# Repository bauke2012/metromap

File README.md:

# metromap
Live metro tracker board

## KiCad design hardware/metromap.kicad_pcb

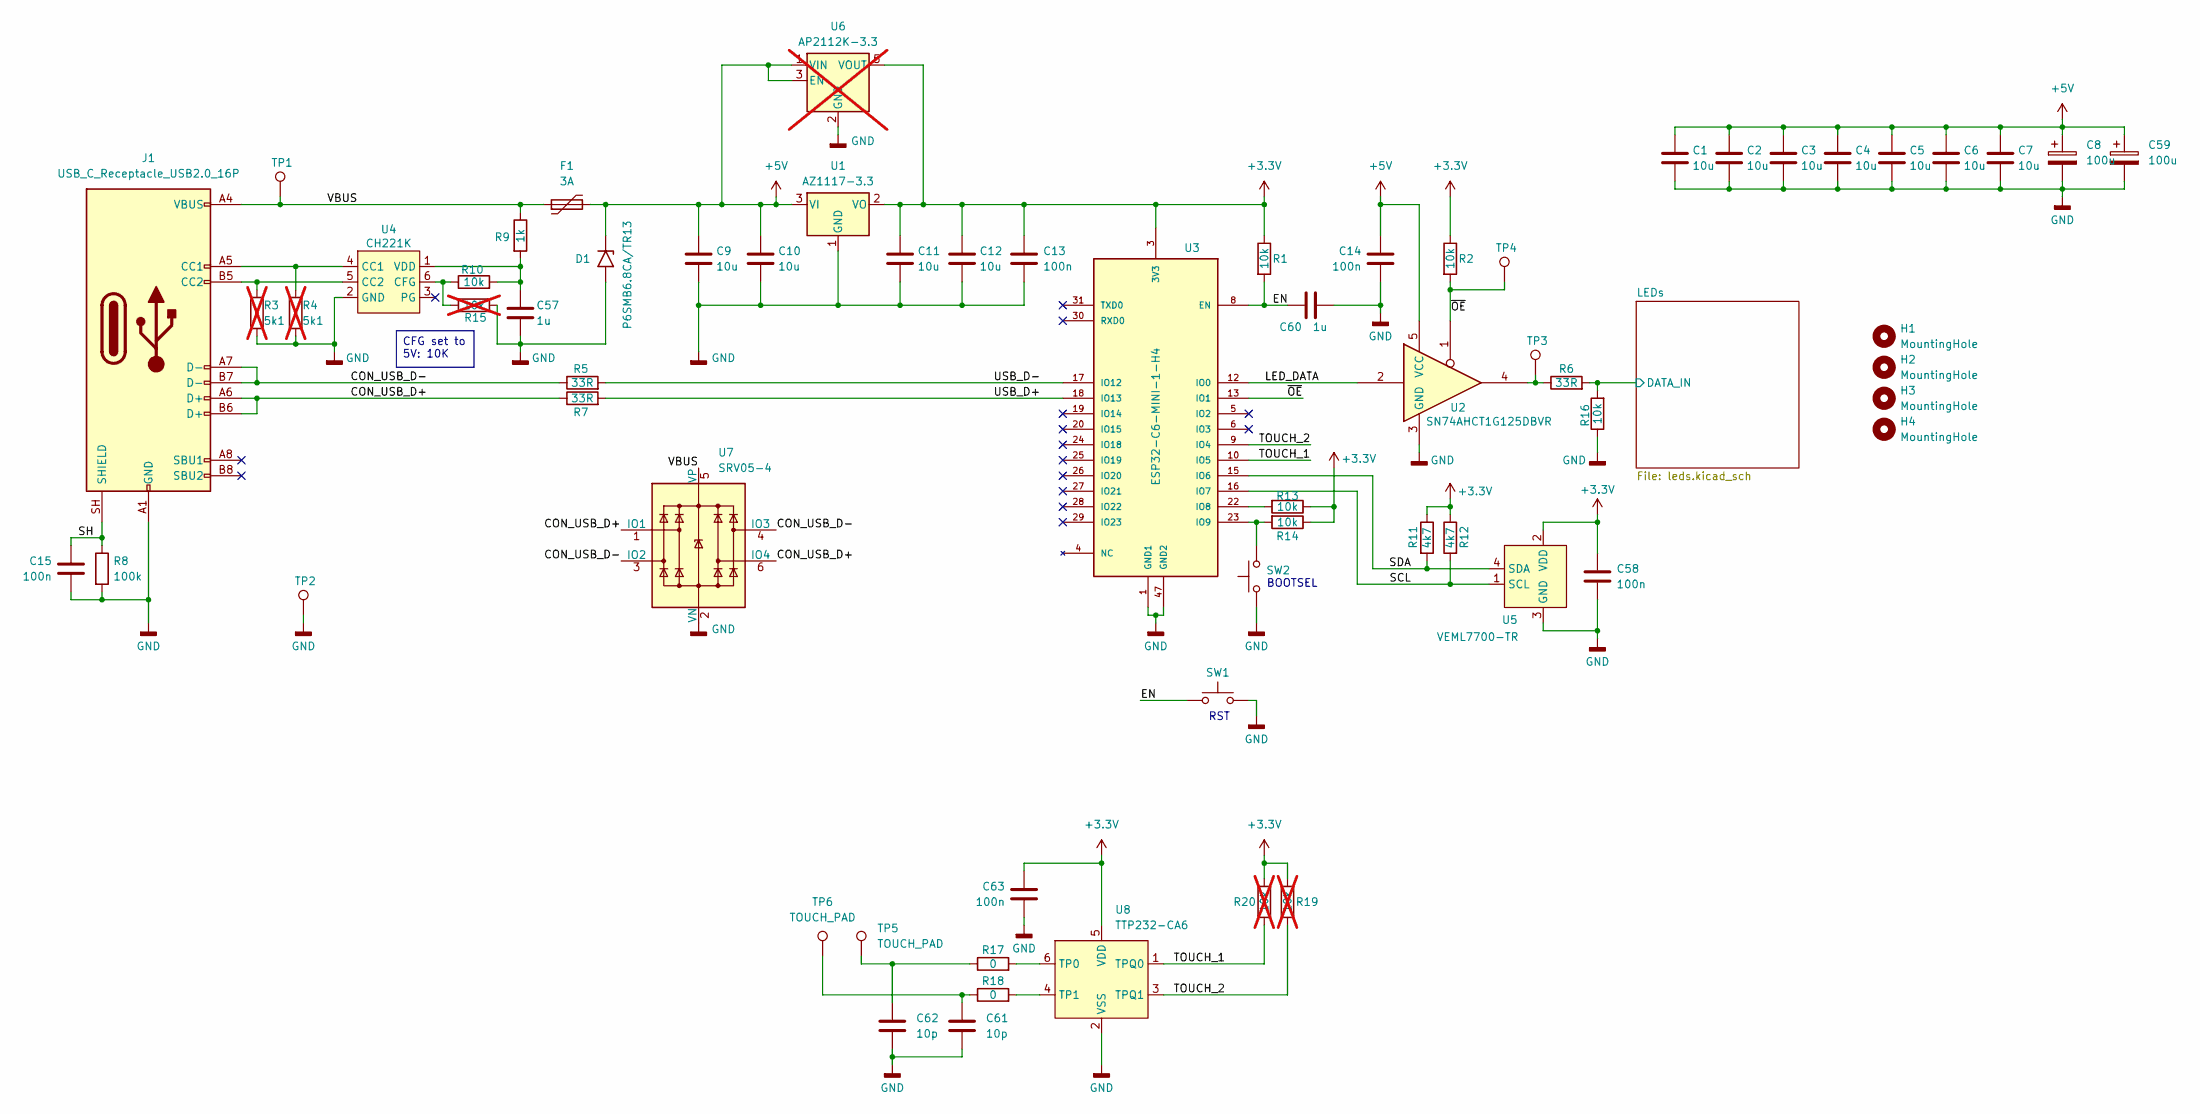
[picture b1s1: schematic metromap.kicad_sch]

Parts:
C1, C2, C3, C4, C5, C6, C7, C9, C10, C11, C12: 10u; C_0805_2012Metric; Manufacturer Part Name 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 CL21A106KAYNNNE; Digikey Part Number 1276-6456-1-ND
C8, C59: 100u; CP_Elec_6.3x7.7; Manufacturer Part Name 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 RVT1V101M0607; Digikey Part Number 732-6390-1-ND
C13, C14, C15, C58, C63: 100n; C_0402_1005Metric; Manufacturer Part Name 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 CL05B104KO5NNNC; Digikey Part Number 1276-1003-1-ND
C57, C60: 1u; C_0603_1608Metric; Manufacturer Part Name 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 CL10A105KB8NNNC; JLCPCB Part Number C15849
C61, C62: 10p; C_0603_1608Metric; Manufacturer Part Name 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 0603CG100J500NT; JLCPCB Part Number C1634
D1: P6SMB6.8CA/TR13; D_SMB; Manufacturer Part Name 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 P6SMB6.8CA/TR13; JLCPCB Part Number C78395
F1: 3A; Fuse_1812_4532Metric; Manufacturer Part Name 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 SMD1812B300TFT; JLCPCB Part Number C269149
H1, H2, H3, H4: MountingHole; MountingHole_3.2mm_M3
J1: USB_C_Receptacle_USB2.0_16P; GCT_USB4800-03-A_REVA; Manufacturer Part Name 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 USB4800-03-A; Digikey Part Number 2073-USB4800-03-ACT-ND
R1, R2, R10, R13, R14, R16: 10k; R_0603_1608Metric; Manufacturer Part Name 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 0603WAF1002T5E; JLCPCB Part Number C25804
R3, R4: 5k1; R_0603_1608Metric; Manufacturer Part Name 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 0603WAF5101T5E; Digikey Part Number 311-5.10KHRCT-ND; not fitted
R5, R7: 33R; R_0603_1608Metric; Manufacturer Part Name 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 0603WAF330JT5E; Digikey Part Number 13-RC0603FR-0733RLCT-ND
R6: 33R; R_0603_1608Metric; Manufacturer Part Name 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 0603WAF330JT5E; JLCPCB Part Number C23140
R8: 100k; R_0603_1608Metric; Manufacturer Part Name 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 0603WAF1003T5E; JLCPCB Part Number C25803
R9: 1k; R_0603_1608Metric; Manufacturer Part Name 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 0603WAF1001T5E; JLCPCB Part Number C21190
R11, R12: 4k7; R_0603_1608Metric; Manufacturer Part Name 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 0603WAF4701T5E; JLCPCB Part Number C23162
R15, R19, R20: 10k; R_0603_1608Metric; Manufacturer Part Name 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 0603WAF1002T5E; JLCPCB Part Number C25804; not fitted
R17, R18: 0; R_0603_1608Metric; Manufacturer Part Name 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 0603WAF0000T5E; JLCPCB Part Number C21189
SW1, SW2: XUNPU_TS-1088-AR02016; TS-1088-AR02016; Manufacturer Part Name 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 TS-1088-AR02016; JLCPCB Part Number C720477
TP1, TP2, TP3, TP4: TestPoint_Pad_D2.0mm
TP5, TP6: TOUCH_PAD
U1: AZ1117-3.3; SOT-223-3_TabPin2; Manufacturer Part Name 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 AMS1117-3.3; Digikey Part Number AZ1117CH-3.3TRG1DICT-ND
U2: SN74AHCT1G125DBVR; SOT-23-5; Manufacturer Part Name 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 SN74AHCT1G125DBVR; JLCPCB Part Number C7484
U3: ESP32-C6-MINI-1-H4; XCVR_ESP32-C6-MINI-1-H4; Manufacturer Part Name 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 ESP32-C6-MINI-1-H4; Digikey Part Number 1965-ESP32-C6-MINI-1-H4CT-ND
U4: CH221K; SOT-23-6; Manufacturer Part Name 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 CH221K; JLCPCB Part Number C5125736
U5: VEML7700-TR; XDCR_VEML7700-TR; Manufacturer Part Name 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 VEML7700-TR; JLCPCB Part Number C504893
U6: AP2112K-3.3; SOT-23-5; Manufacturer Part Name 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 AP2112K-3.3TRG1; JLCPCB Part Number C51118; not fitted
U7: SRV05-4; SOT-23-6; Manufacturer Part Name 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 SRV05-4-P-T7; JLCPCB Part Number C85364
U8: TTP232-CA6; SOT-23-6; Manufacturer Part Name 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 TTP232-CA6; JLCPCB Part Number C134176

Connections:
+3.3V: C11.1, C12.1, C13.1, C58.1, C63.1, R1.1, R2.1, R11.1, R12.1, R13.1, R14.1, R19.1, R20.1, U1.2 (VO), U3.3 (3V3), U5.2 (VDD), U6.5 (VOUT), U8.5 (VDD)
+5V: C1.1, C2.1, C3.1, C4.1, C5.1, C6.1, C7.1, C8.1, C9.1, C10.1, C14.1, C59.1, D1.1 (A1), F1.2, U1.3 (VI), U2.5 (VCC), U6.1 (VIN), U6.3 (EN); also elsewhere on the board
/CON_USB_D+: J1.A6 (D+), J1.B6 (D+), R7.1, U7.1 (IO1), U7.6 (IO4)
/CON_USB_D-: J1.A7 (D-), J1.B7 (D-), R5.1, U7.3 (IO2), U7.4 (IO3)
/EN: C60.1, R1.2, SW1.1, U3.8 (EN)
/LED_DATA: U2.2, U3.12 (IO0)
/LEDs/DATA_IN: R6.2, R16.2; also elsewhere on the board
/SCL: R12.2, U3.16 (IO7), U5.1 (SCL)
/SDA: R11.2, U3.15 (IO6), U5.4 (SDA)
/SH: C15.1, J1.SH (SHIELD), R8.1
/TOUCH_1: R20.2, U3.10 (IO5), U8.1 (TPQ0)
/TOUCH_2: R19.2, U3.9 (IO4), U8.3 (TPQ1)
/USB_D+: R7.2, U3.18 (IO13)
/USB_D-: R5.2, U3.17 (IO12)
/VBUS: F1.1, J1.A4 (VBUS), J1.A9 (VBUS), J1.B4 (VBUS), J1.B9 (VBUS), R9.1, TP1.1 (1_1), U7.5 (VP)
/~OE: R2.2, TP4.1 (1_1), U2.1, U3.13 (IO1)
GND: C1.2, C2.2, C3.2, C4.2, C5.2, C6.2, C7.2, C8.2, C9.2, C10.2, C11.2, C12.2, C13.2, C14.2, C15.2, C57.2, C58.2, C59.2, C60.2, C61.2, C62.2, C63.2, D1.2 (A2), J1.A1 (GND), J1.A12 (GND), J1.B1 (GND), J1.B12 (GND), R3.2, R4.2, R8.2, R15.1, R16.1, SW1.2, SW2.1, TP2.1 (1_1), U1.1 (GND), U2.3 (GND), U3.1 (GND1), U3.2 (GND1), U3.11 (GND1), U3.14 (GND1), U3.36 (GND1), U3.37 (GND1), U3.38 (GND1), U3.39 (GND1), U3.40 (GND1), U3.41 (GND1), U3.42 (GND1), U3.43 (GND1), U3.44 (GND1), U3.45 (GND1), U3.46 (GND1), U3.47 (GND2), U3.48 (GND2), U3.49_1 (GND2), U3.49_2 (GND2), U3.49_3 (GND2), U3.49_4 (GND2), U3.49_5 (GND2), U3.49_6 (GND2), U3.49_7 (GND2), U3.49_8 (GND2), U3.49_9 (GND2), U3.50 (GND2), U3.51 (GND2), U3.52 (GND2), U3.53 (GND2), U4.2 (GND), U5.3 (GND), U6.2 (GND), U7.2 (VN), U8.2 (VSS); also elsewhere on the board
unnamed: C61.1, R18.1, TP6.1 (1_1)
unnamed: C62.1, R17.1, TP5.1 (1_1)
unnamed: J1.A5 (CC1), R4.1, U4.4 (CC1)
unnamed: J1.B5 (CC2), R3.1, U4.5 (CC2)
unnamed: R6.1, TP3.1 (1_1), U2.4
unnamed: R13.2, U3.22 (IO8)
unnamed: R14.2, SW2.2, U3.23 (IO9)
unnamed: R10.1, R15.2, U4.6 (CFG)
unnamed: C57.1, R9.2, R10.2, U4.1 (VDD)
unnamed: R17.2, U8.6 (TP0)
unnamed: R18.2, U8.4 (TP1)

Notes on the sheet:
RST
BOOTSEL
CFG set to 5V: 10K

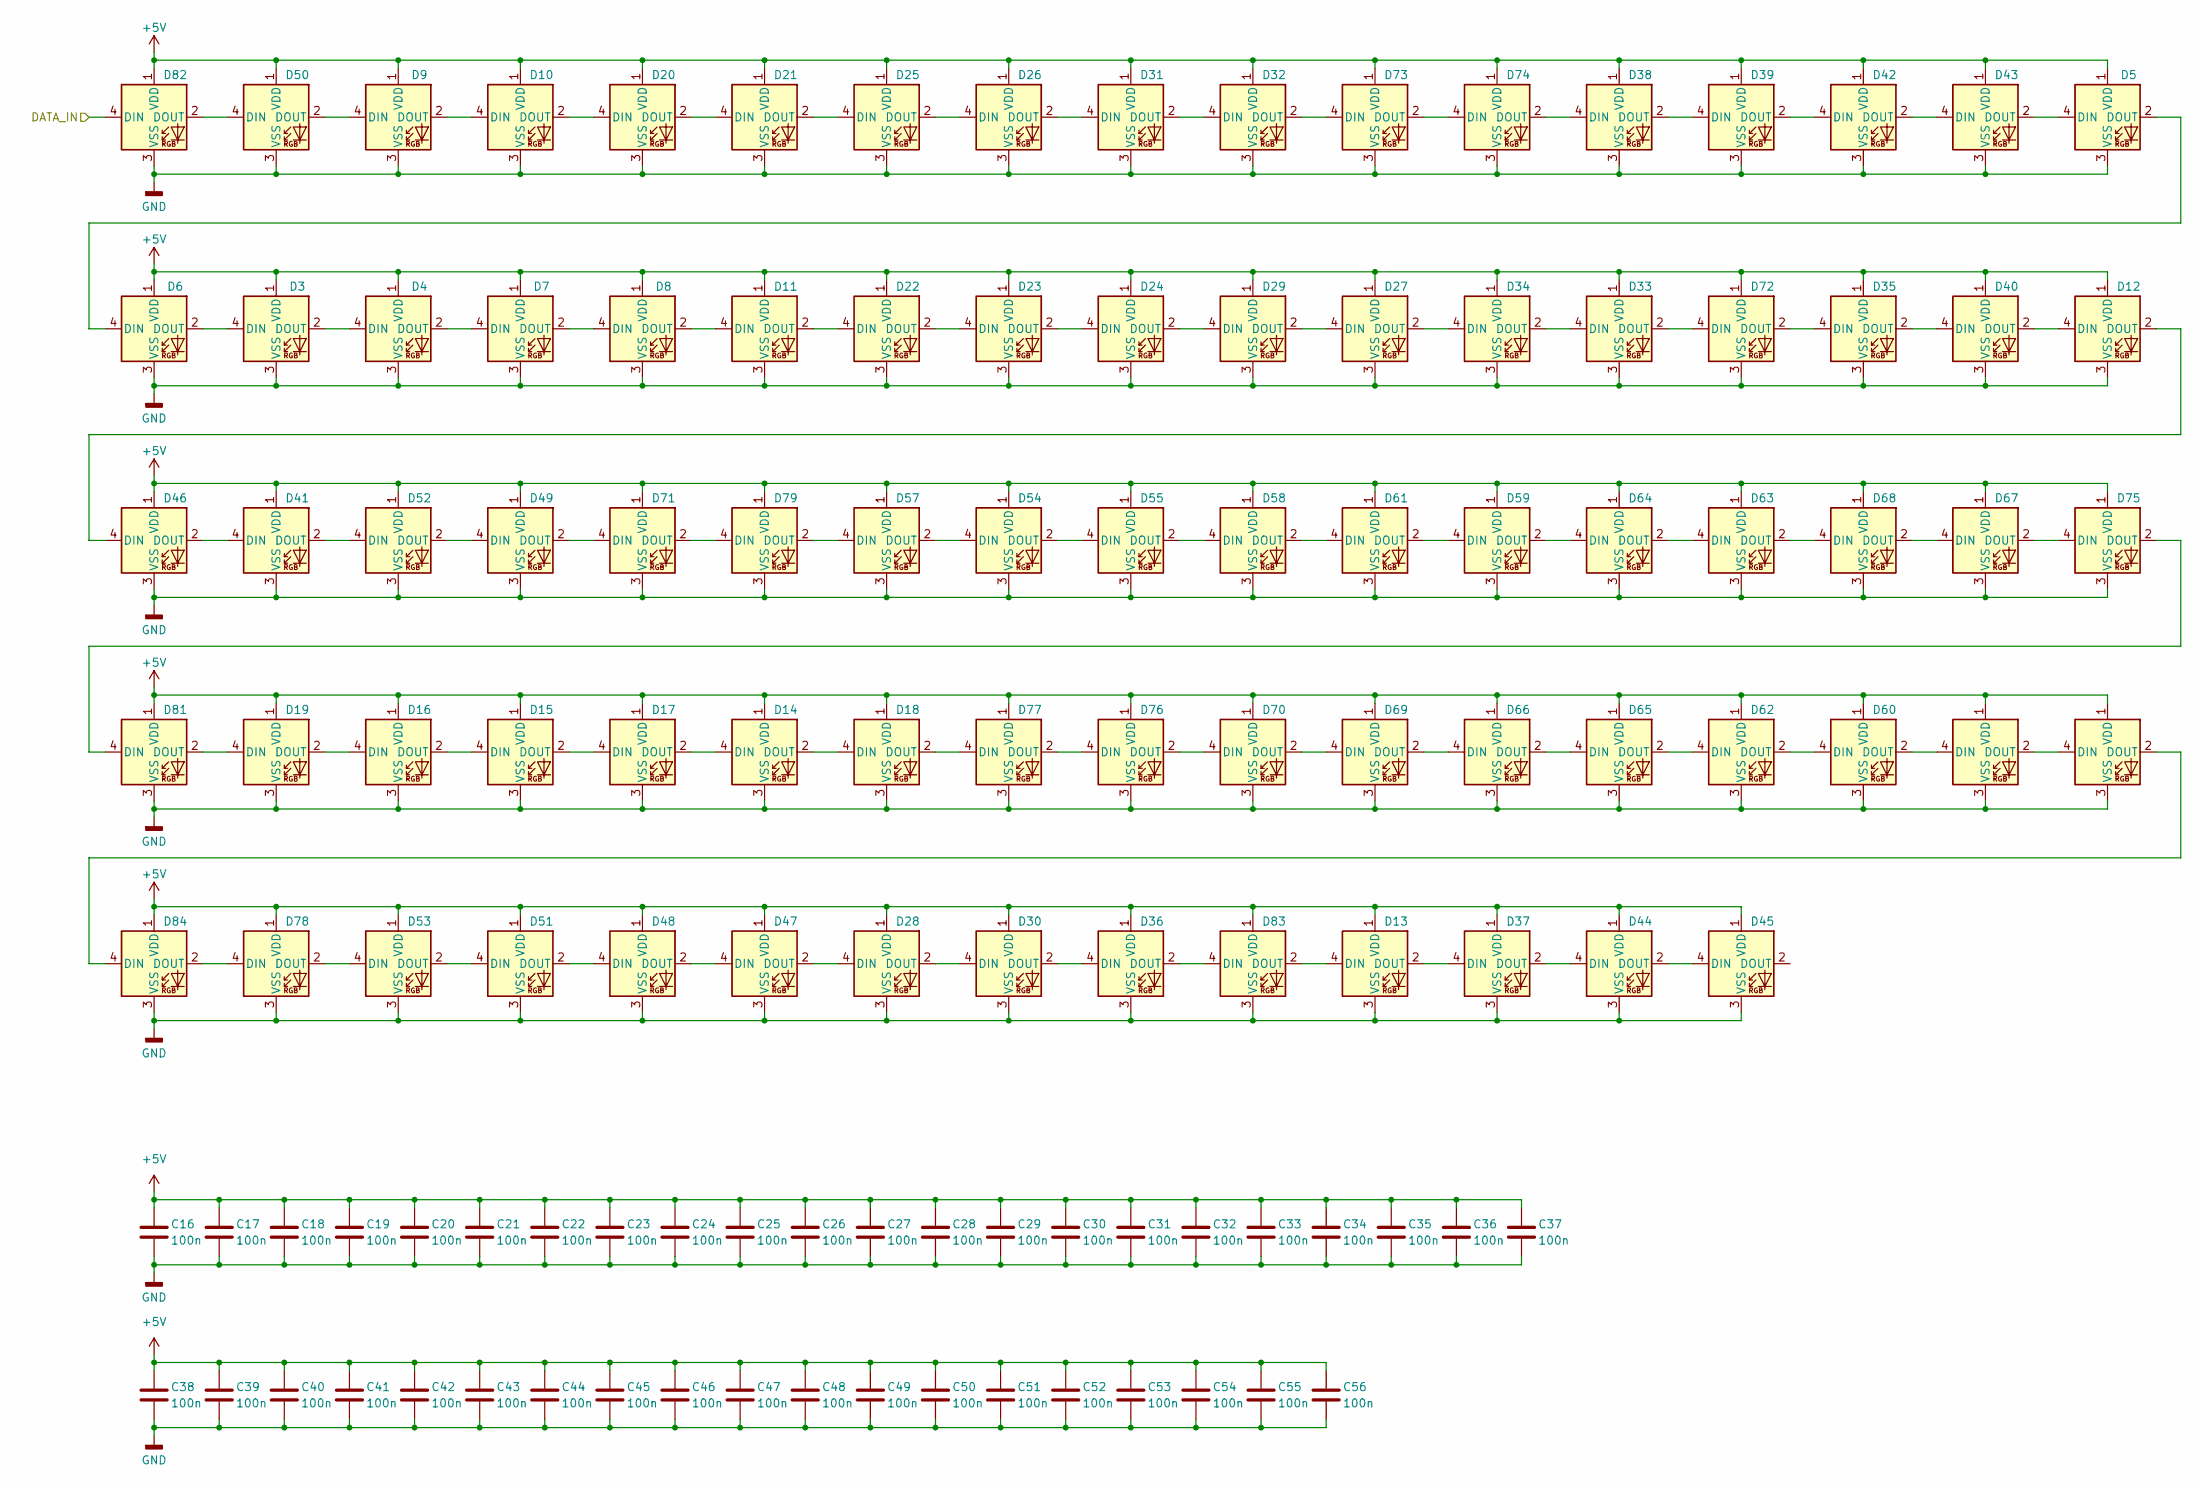
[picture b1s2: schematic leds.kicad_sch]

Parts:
C16, C17, C18, C19, C20, C21, C22, C23, C24, C25, C26, C27, C28, C29, C30, C31, C32, C33, C34, C35, C36, C37, C38, C39, C40, C41, C42, C43, C44, C45, C46, C47, C48, C49, C50, C51, C52, C53, C54, C55, C56: 100n; C_0402_1005Metric; Manufacturer Part Name 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 CL05B104KO5NNNC; Digikey Part Number 1276-1003-1-ND
D3, D4, D5, D6, D7, D8, D9, D10, D11, D12, D13, D14, D15, D16, D17, D18, D19, D20, D21, D22, D23, D24, D25, D26, D27, D28, D29, D30, D31, D32, D33, D34, D35, D36, D37, D38, D39, D40, D41, D42, D43, D44, D45, D46, D47, D48, D49, D50, D51, D52, D53, D54, D55, D56, D57, D58, D59, D60, D61, D62, D63, D64, D65, D66, D67, D68, D69, D70, D71, D72, D73, D74, D75, D76, D77, D78, D79, D80, D81, D82, D83, D84: SK6812-EC20; RGB_LED_2020; Manufacturer Part Name 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 SK6812-EC20; Digikey Part Number 1830-IN-PI20TAT5R5G5BCT-ND

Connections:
+5V: C16.1, C17.1, C18.1, C19.1, C20.1, C21.1, C22.1, C23.1, C24.1, C25.1, C26.1, C27.1, C28.1, C29.1, C30.1, C31.1, C32.1, C33.1, C34.1, C35.1, C36.1, C37.1, C38.1, C39.1, C40.1, C41.1, C42.1, C43.1, C44.1, C45.1, C46.1, C47.1, C48.1, C49.1, C50.1, C51.1, C52.1, C53.1, C54.1, C55.1, C56.1, D3.1 (VDD), D4.1 (VDD), D5.1 (VDD), D6.1 (VDD), D7.1 (VDD), D8.1 (VDD), D9.1 (VDD), D10.1 (VDD), D11.1 (VDD), D12.1 (VDD), D13.1 (VDD), D14.1 (VDD), D15.1 (VDD), D16.1 (VDD), D17.1 (VDD), D18.1 (VDD), D19.1 (VDD), D20.1 (VDD), D21.1 (VDD), D22.1 (VDD), D23.1 (VDD), D24.1 (VDD), D25.1 (VDD), D26.1 (VDD), D27.1 (VDD), D28.1 (VDD), D29.1 (VDD), D30.1 (VDD), D31.1 (VDD), D32.1 (VDD), D33.1 (VDD), D34.1 (VDD), D35.1 (VDD), D36.1 (VDD), D37.1 (VDD), D38.1 (VDD), D39.1 (VDD), D40.1 (VDD), D41.1 (VDD), D42.1 (VDD), D43.1 (VDD), D44.1 (VDD), D45.1 (VDD), D46.1 (VDD), D47.1 (VDD), D48.1 (VDD), D49.1 (VDD), D50.1 (VDD), D51.1 (VDD), D52.1 (VDD), D53.1 (VDD), D54.1 (VDD), D55.1 (VDD), D56.1 (VDD), D57.1 (VDD), D58.1 (VDD), D59.1 (VDD), D60.1 (VDD), D61.1 (VDD), D62.1 (VDD), D63.1 (VDD), D64.1 (VDD), D65.1 (VDD), D66.1 (VDD), D67.1 (VDD), D68.1 (VDD), D69.1 (VDD), D70.1 (VDD), D71.1 (VDD), D72.1 (VDD), D73.1 (VDD), D74.1 (VDD), D75.1 (VDD), D76.1 (VDD), D77.1 (VDD), D78.1 (VDD), D79.1 (VDD), D80.1 (VDD), D81.1 (VDD), D82.1 (VDD), D83.1 (VDD), D84.1 (VDD); also elsewhere on the board
/LEDs/DATA_IN: D82.4 (DIN); also elsewhere on the board
GND: C16.2, C17.2, C18.2, C19.2, C20.2, C21.2, C22.2, C23.2, C24.2, C25.2, C26.2, C27.2, C28.2, C29.2, C30.2, C31.2, C32.2, C33.2, C34.2, C35.2, C36.2, C37.2, C38.2, C39.2, C40.2, C41.2, C42.2, C43.2, C44.2, C45.2, C46.2, C47.2, C48.2, C49.2, C50.2, C51.2, C52.2, C53.2, C54.2, C55.2, C56.2, D3.3 (VSS), D4.3 (VSS), D5.3 (VSS), D6.3 (VSS), D7.3 (VSS), D8.3 (VSS), D9.3 (VSS), D10.3 (VSS), D11.3 (VSS), D12.3 (VSS), D13.3 (VSS), D14.3 (VSS), D15.3 (VSS), D16.3 (VSS), D17.3 (VSS), D18.3 (VSS), D19.3 (VSS), D20.3 (VSS), D21.3 (VSS), D22.3 (VSS), D23.3 (VSS), D24.3 (VSS), D25.3 (VSS), D26.3 (VSS), D27.3 (VSS), D28.3 (VSS), D29.3 (VSS), D30.3 (VSS), D31.3 (VSS), D32.3 (VSS), D33.3 (VSS), D34.3 (VSS), D35.3 (VSS), D36.3 (VSS), D37.3 (VSS), D38.3 (VSS), D39.3 (VSS), D40.3 (VSS), D41.3 (VSS), D42.3 (VSS), D43.3 (VSS), D44.3 (VSS), D45.3 (VSS), D46.3 (VSS), D47.3 (VSS), D48.3 (VSS), D49.3 (VSS), D50.3 (VSS), D51.3 (VSS), D52.3 (VSS), D53.3 (VSS), D54.3 (VSS), D55.3 (VSS), D56.3 (VSS), D57.3 (VSS), D58.3 (VSS), D59.3 (VSS), D60.3 (VSS), D61.3 (VSS), D62.3 (VSS), D63.3 (VSS), D64.3 (VSS), D65.3 (VSS), D66.3 (VSS), D67.3 (VSS), D68.3 (VSS), D69.3 (VSS), D70.3 (VSS), D71.3 (VSS), D72.3 (VSS), D73.3 (VSS), D74.3 (VSS), D75.3 (VSS), D76.3 (VSS), D77.3 (VSS), D78.3 (VSS), D79.3 (VSS), D80.3 (VSS), D81.3 (VSS), D82.3 (VSS), D83.3 (VSS), D84.3 (VSS); also elsewhere on the board
unnamed: D3.4 (DIN), D6.2 (DOUT)
unnamed: D3.2 (DOUT), D4.4 (DIN)
unnamed: D4.2 (DOUT), D7.4 (DIN)
unnamed: D5.2 (DOUT), D6.4 (DIN)
unnamed: D7.2 (DOUT), D8.4 (DIN)
unnamed: D9.2 (DOUT), D10.4 (DIN)
unnamed: D10.2 (DOUT), D20.4 (DIN)
unnamed: D8.2 (DOUT), D11.4 (DIN)
unnamed: D11.2 (DOUT), D22.4 (DIN)
unnamed: D12.4 (DIN), D40.2 (DOUT)
unnamed: D12.2 (DOUT), D46.4 (DIN)
unnamed: D13.4 (DIN), D83.2 (DOUT)
unnamed: D13.2 (DOUT), D37.4 (DIN)
unnamed: D14.4 (DIN), D17.2 (DOUT)
unnamed: D14.2 (DOUT), D18.4 (DIN)
unnamed: D15.4 (DIN), D16.2 (DOUT)
unnamed: D15.2 (DOUT), D17.4 (DIN)
unnamed: D16.4 (DIN), D19.2 (DOUT)
unnamed: D18.2 (DOUT), D77.4 (DIN)
unnamed: D19.4 (DIN), D81.2 (DOUT)
unnamed: D20.2 (DOUT), D21.4 (DIN)
unnamed: D21.2 (DOUT), D25.4 (DIN)
unnamed: D22.2 (DOUT), D23.4 (DIN)
unnamed: D23.2 (DOUT), D24.4 (DIN)
unnamed: D24.2 (DOUT), D29.4 (DIN)
unnamed: D25.2 (DOUT), D26.4 (DIN)
unnamed: D26.2 (DOUT), D31.4 (DIN)
unnamed: D27.4 (DIN), D29.2 (DOUT)
unnamed: D27.2 (DOUT), D34.4 (DIN)
unnamed: D28.4 (DIN), D47.2 (DOUT)
unnamed: D28.2 (DOUT), D30.4 (DIN)
unnamed: D30.2 (DOUT), D36.4 (DIN)
unnamed: D31.2 (DOUT), D32.4 (DIN)
unnamed: D32.2 (DOUT), D73.4 (DIN)
unnamed: D33.4 (DIN), D34.2 (DOUT)
unnamed: D33.2 (DOUT), D72.4 (DIN)
unnamed: D35.4 (DIN), D72.2 (DOUT)
unnamed: D35.2 (DOUT), D40.4 (DIN)
unnamed: D36.2 (DOUT), D83.4 (DIN)
unnamed: D37.2 (DOUT), D44.4 (DIN)
unnamed: D38.4 (DIN), D74.2 (DOUT)
unnamed: D38.2 (DOUT), D39.4 (DIN)
unnamed: D39.2 (DOUT), D42.4 (DIN)
unnamed: D41.4 (DIN), D46.2 (DOUT)
unnamed: D41.2 (DOUT), D52.4 (DIN)
unnamed: D42.2 (DOUT), D43.4 (DIN)
unnamed: D5.4 (DIN), D43.2 (DOUT)
unnamed: D44.2 (DOUT), D45.4 (DIN)
unnamed: D47.4 (DIN), D48.2 (DOUT)
unnamed: D48.4 (DIN), D51.2 (DOUT)
unnamed: D49.4 (DIN), D52.2 (DOUT)
unnamed: D49.2 (DOUT), D71.4 (DIN)
unnamed: D50.4 (DIN), D82.2 (DOUT)
unnamed: D9.4 (DIN), D50.2 (DOUT)
unnamed: D51.4 (DIN), D53.2 (DOUT)
unnamed: D53.4 (DIN), D78.2 (DOUT)
unnamed: D54.4 (DIN), D57.2 (DOUT)
unnamed: D54.2 (DOUT), D55.4 (DIN)
unnamed: D55.2 (DOUT), D58.4 (DIN)
unnamed: D56.4 (DIN), D80.2 (DOUT)
unnamed: D56.2 (DOUT), D84.4 (DIN)
unnamed: D57.4 (DIN), D79.2 (DOUT)
unnamed: D58.2 (DOUT), D61.4 (DIN)
unnamed: D59.4 (DIN), D61.2 (DOUT)
unnamed: D59.2 (DOUT), D64.4 (DIN)
unnamed: D60.4 (DIN), D62.2 (DOUT)
unnamed: D60.2 (DOUT), D80.4 (DIN)
unnamed: D62.4 (DIN), D65.2 (DOUT)
unnamed: D63.4 (DIN), D64.2 (DOUT)
unnamed: D63.2 (DOUT), D68.4 (DIN)
unnamed: D65.4 (DIN), D66.2 (DOUT)
unnamed: D66.4 (DIN), D69.2 (DOUT)
unnamed: D67.4 (DIN), D68.2 (DOUT)
unnamed: D67.2 (DOUT), D75.4 (DIN)
unnamed: D69.4 (DIN), D70.2 (DOUT)
unnamed: D70.4 (DIN), D76.2 (DOUT)
unnamed: D71.2 (DOUT), D79.4 (DIN)
unnamed: D73.2 (DOUT), D74.4 (DIN)
unnamed: D75.2 (DOUT), D81.4 (DIN)
unnamed: D76.4 (DIN), D77.2 (DOUT)
unnamed: D78.4 (DIN), D84.2 (DOUT)

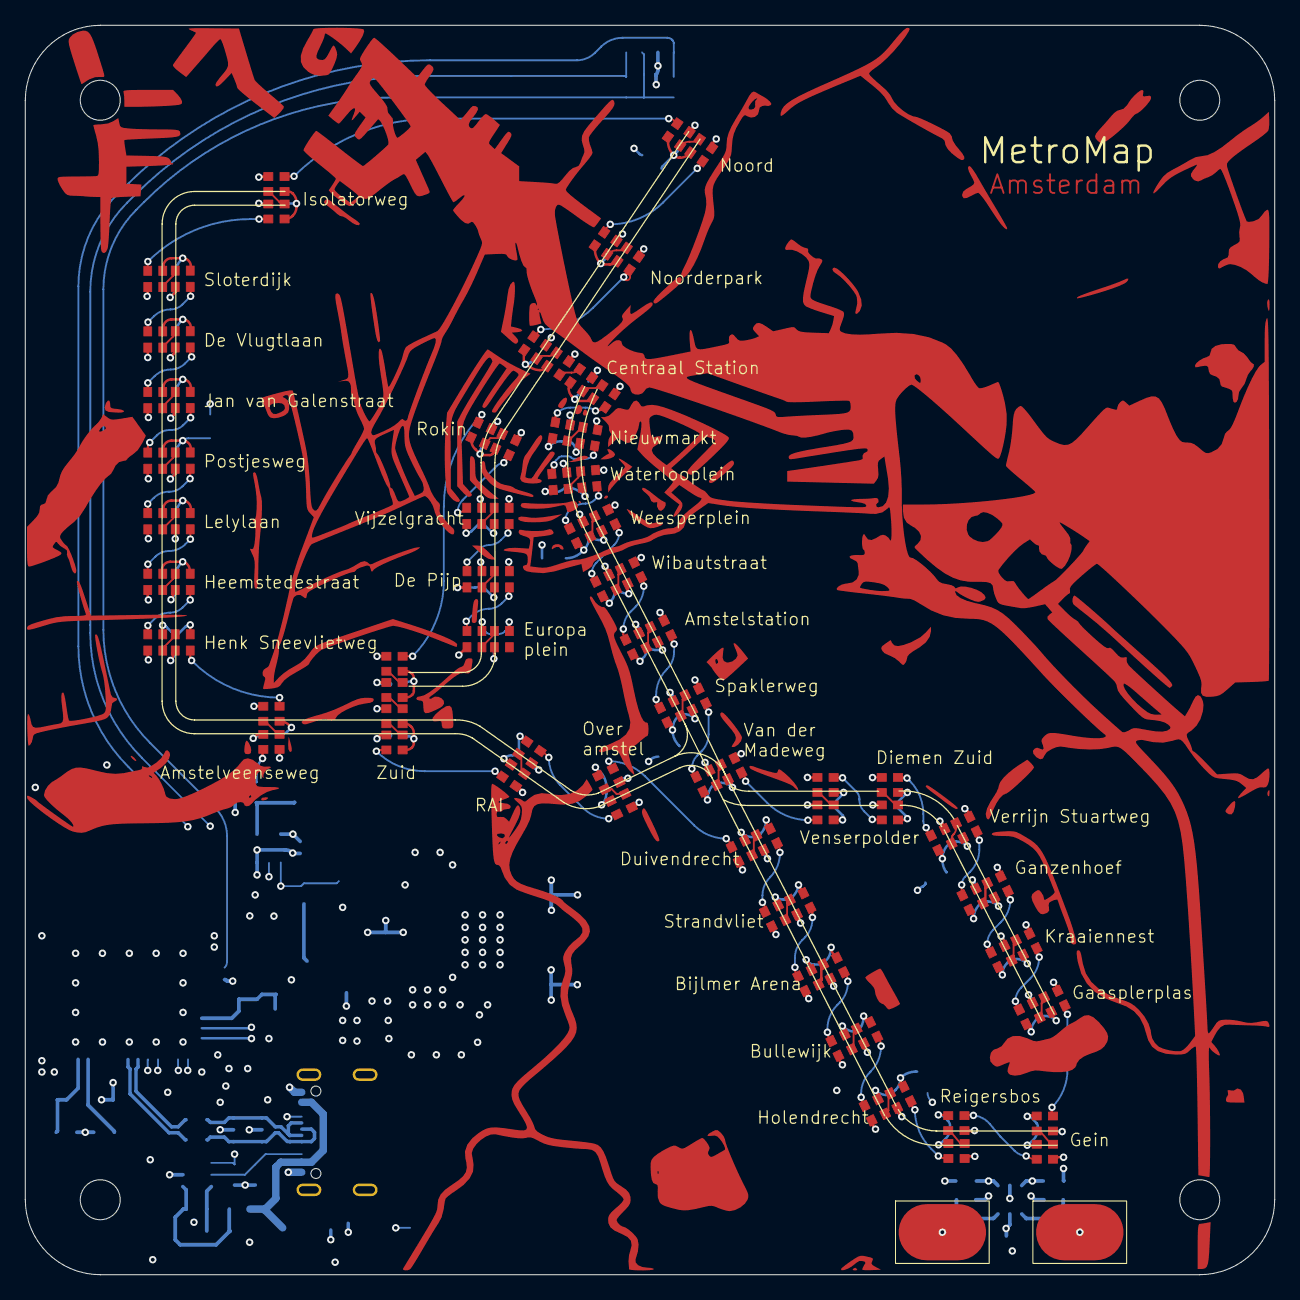
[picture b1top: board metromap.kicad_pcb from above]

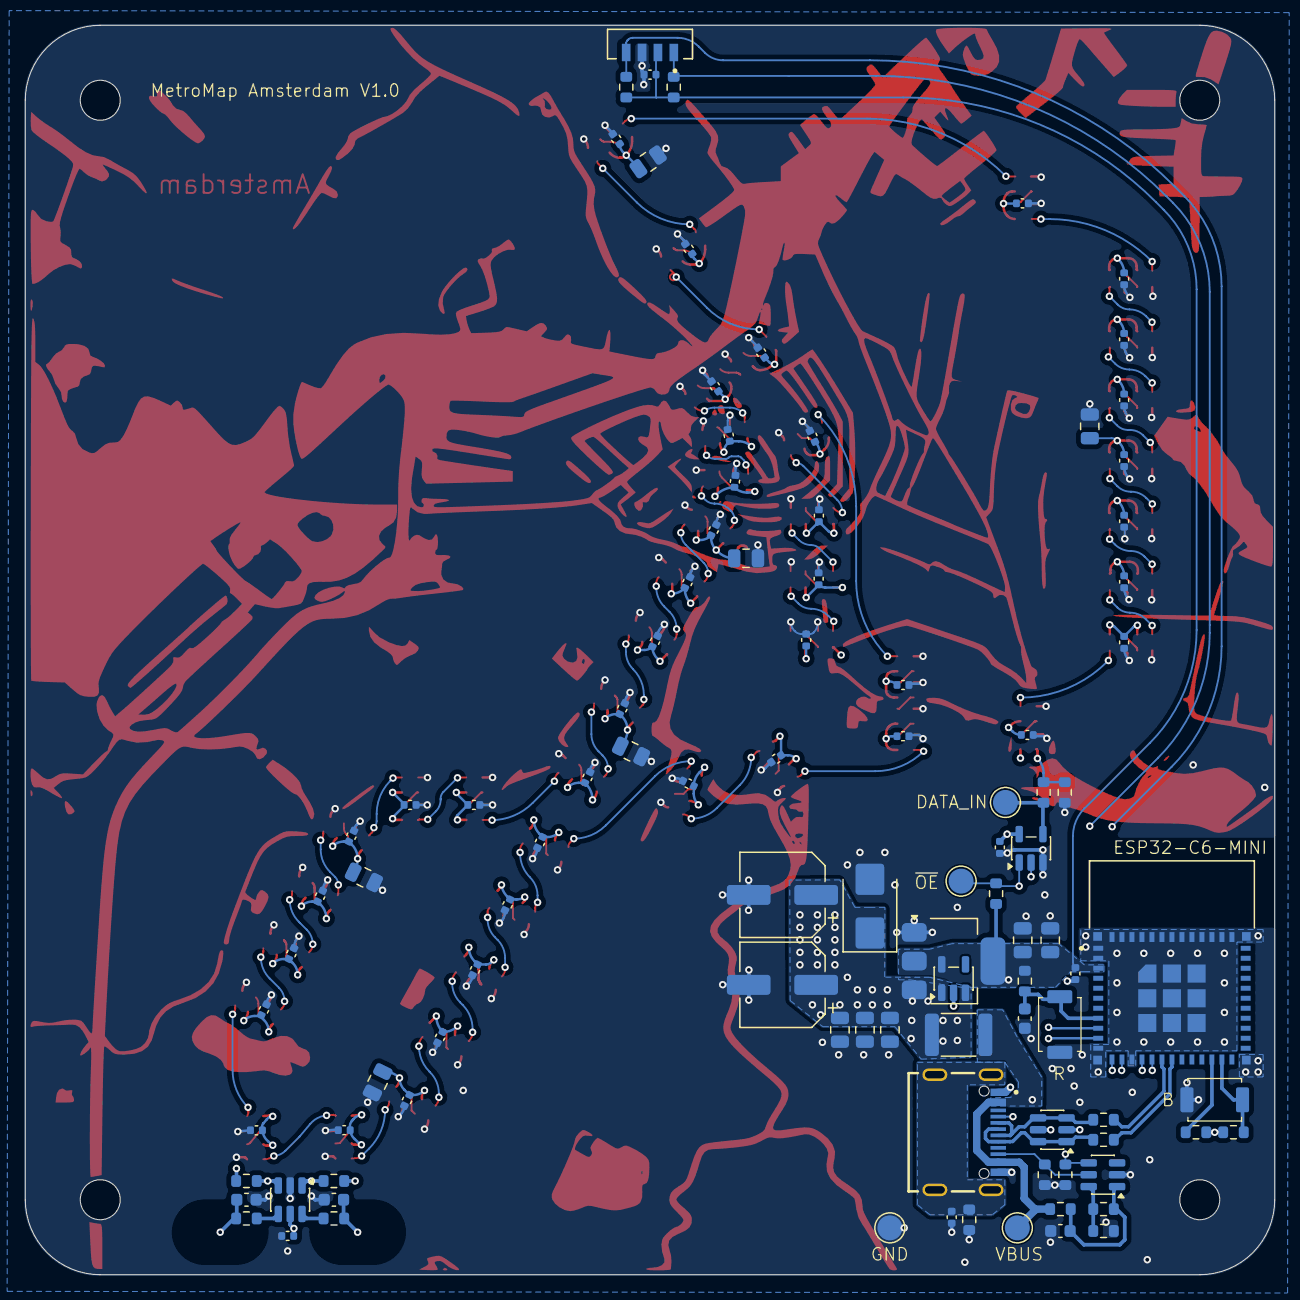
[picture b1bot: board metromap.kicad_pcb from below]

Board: 4 copper layers, 100.0 x 100.0 mm, 188 parts (100 on the bottom side), 109 nets.

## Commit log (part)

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2026-06-25 Routed half of leds
